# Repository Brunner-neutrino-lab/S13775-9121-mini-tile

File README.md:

# S13775-9121-mini-tile
Carrier board and mounting tile for S13775-9121-mini-tile

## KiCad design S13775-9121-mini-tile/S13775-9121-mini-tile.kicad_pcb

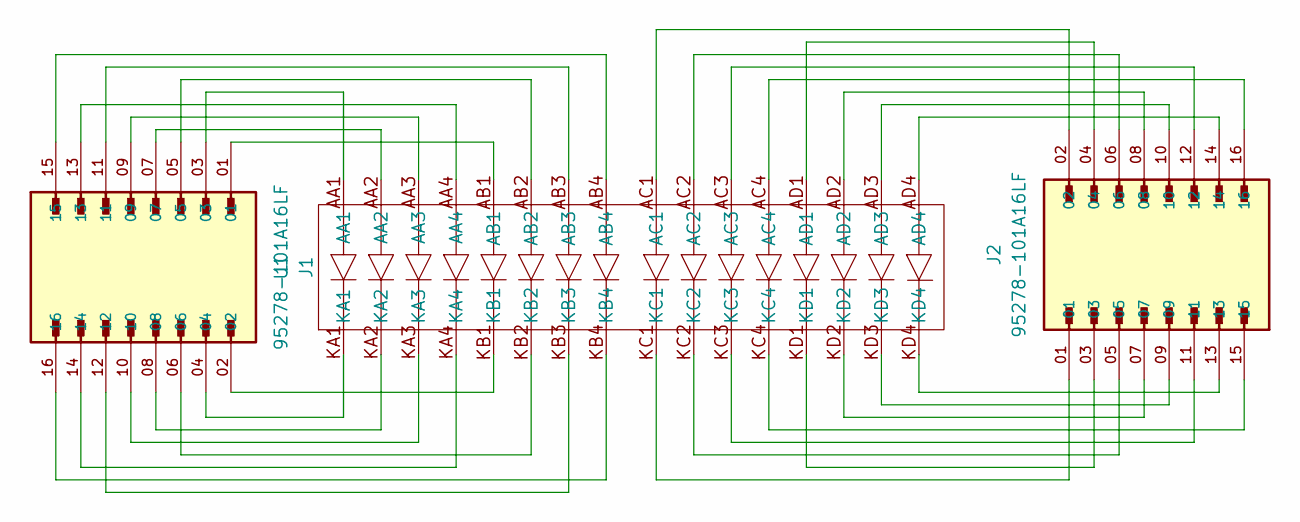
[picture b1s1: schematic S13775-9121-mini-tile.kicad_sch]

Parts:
J1, J2: 95278-101A16LF; AMPHENOL_95278-101A16LF; PARTREV AH
U1: mini-tile

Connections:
unnamed: J1.01, U1.AB1
unnamed: J1.02, U1.KB1
unnamed: J1.03, U1.AA1
unnamed: J1.04, U1.KA1
unnamed: J1.05, U1.AB2
unnamed: J1.06, U1.KB2
unnamed: J1.07, U1.AA2
unnamed: J1.08, U1.KA2
unnamed: J1.09, U1.AA3
unnamed: J1.10, U1.KA3
unnamed: J1.11, U1.AB3
unnamed: J1.12, U1.KB3
unnamed: J1.13, U1.AA4
unnamed: J1.14, U1.KA4
unnamed: J1.15, U1.AB4
unnamed: J1.16, U1.KB4
unnamed: J2.01, U1.KC1
unnamed: J2.02, U1.AC1
unnamed: J2.03, U1.KD1
unnamed: J2.04, U1.AD1
unnamed: J2.05, U1.KC2
unnamed: J2.06, U1.AC2
unnamed: J2.07, U1.KD2
unnamed: J2.08, U1.AD2
unnamed: J2.09, U1.KD3
unnamed: J2.10, U1.AD3
unnamed: J2.11, U1.KC3
unnamed: J2.12, U1.AC3
unnamed: J2.13, U1.KD4
unnamed: J2.14, U1.AD4
unnamed: J2.15, U1.KC4
unnamed: J2.16, U1.AC4

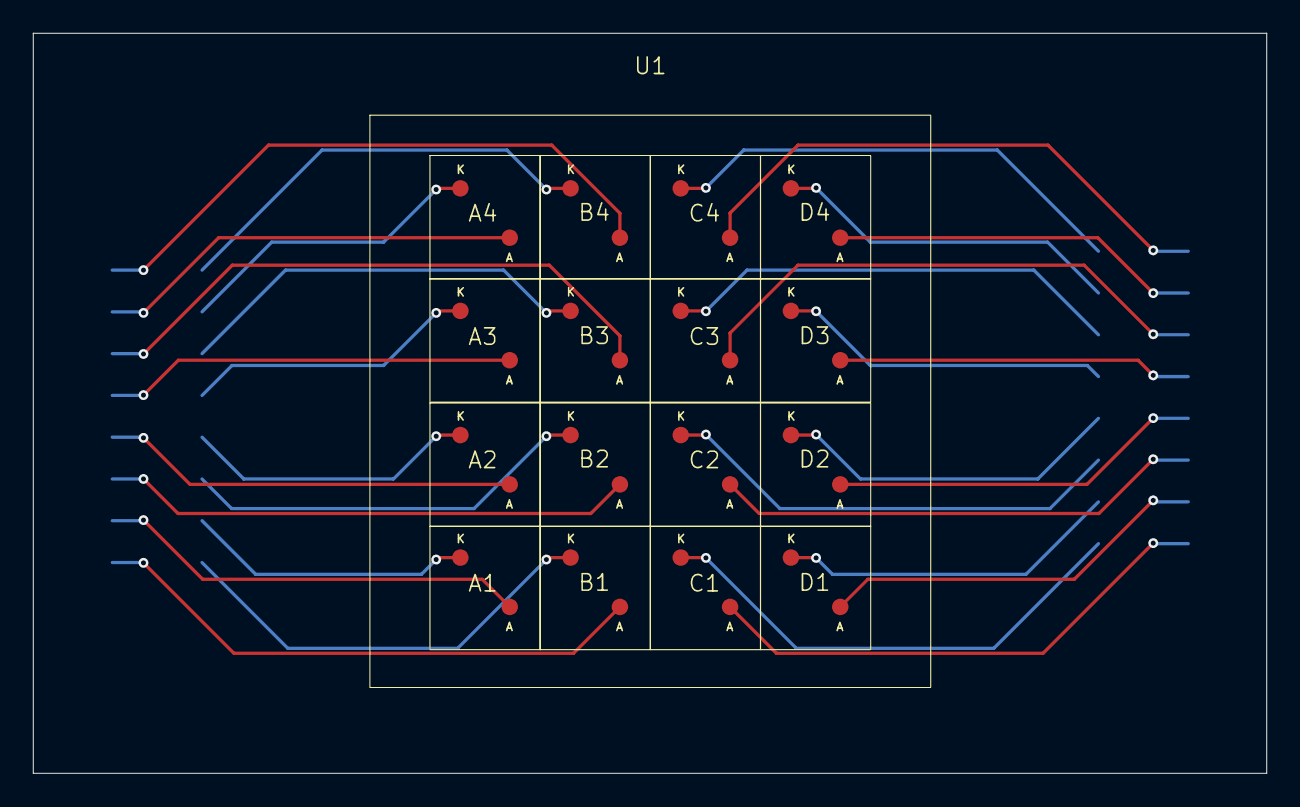
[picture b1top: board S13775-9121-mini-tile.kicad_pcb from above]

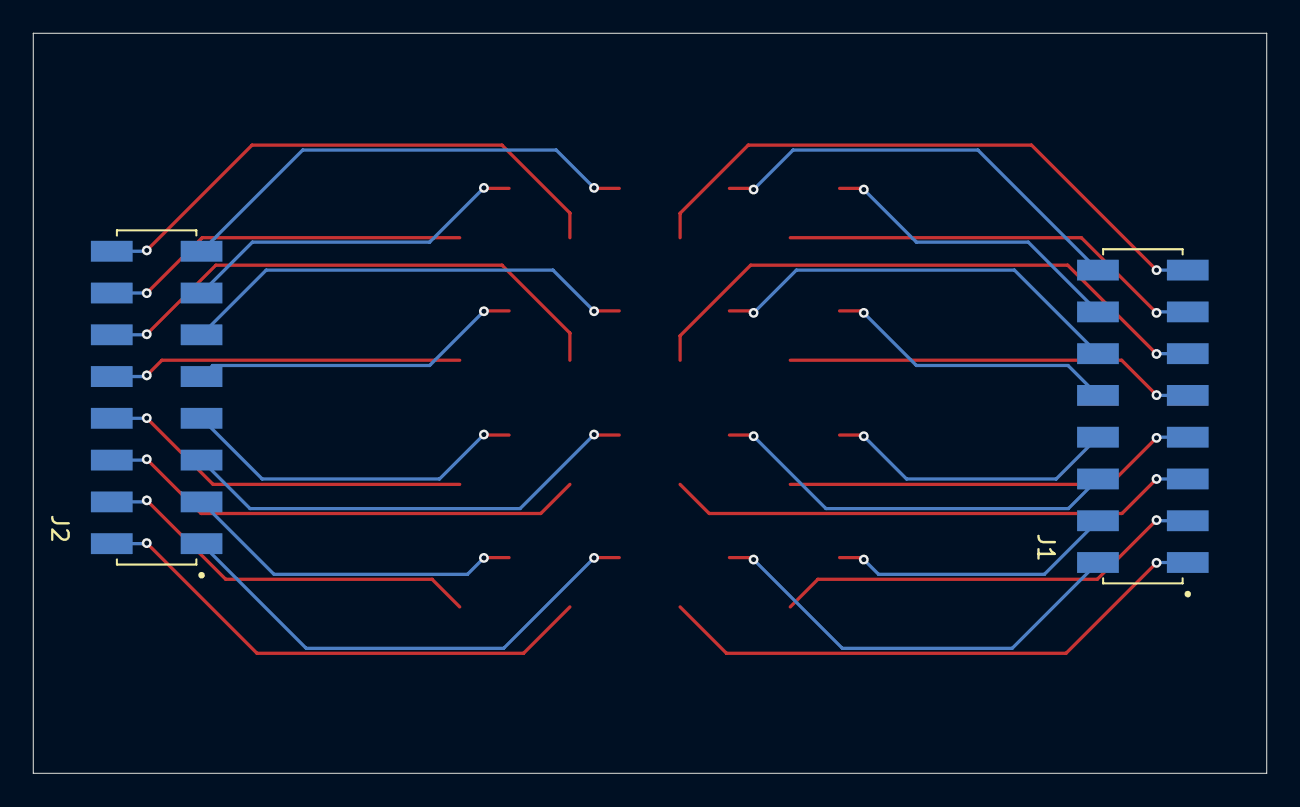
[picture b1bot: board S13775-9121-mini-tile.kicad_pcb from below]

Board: 2 copper layers, 75.0 x 45.0 mm, 3 parts (2 on the bottom side), 32 nets.

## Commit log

2025-06-25 Initial Upload
2025-06-25 Update S13775-9121-mini-tile.kicad_pcb.zip
    Decreased pad diameter
